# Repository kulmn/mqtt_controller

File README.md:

# External device controller with timers and MQTT protocol.

Hardware: 
- Schematic diagram (Autodesk EAGLE) in /schematic/ dir
- MCU: STM32L152CB, STM32F030F4 ([firmware](https://github.com/kulmn/lcd_hd44780_f030x4))
- Ethernet: WIZnet W5500
- Indicator: HD44780 16x2

Firmware:
- GCC Eclipse project, FreeRTOS, LibOpenCM3

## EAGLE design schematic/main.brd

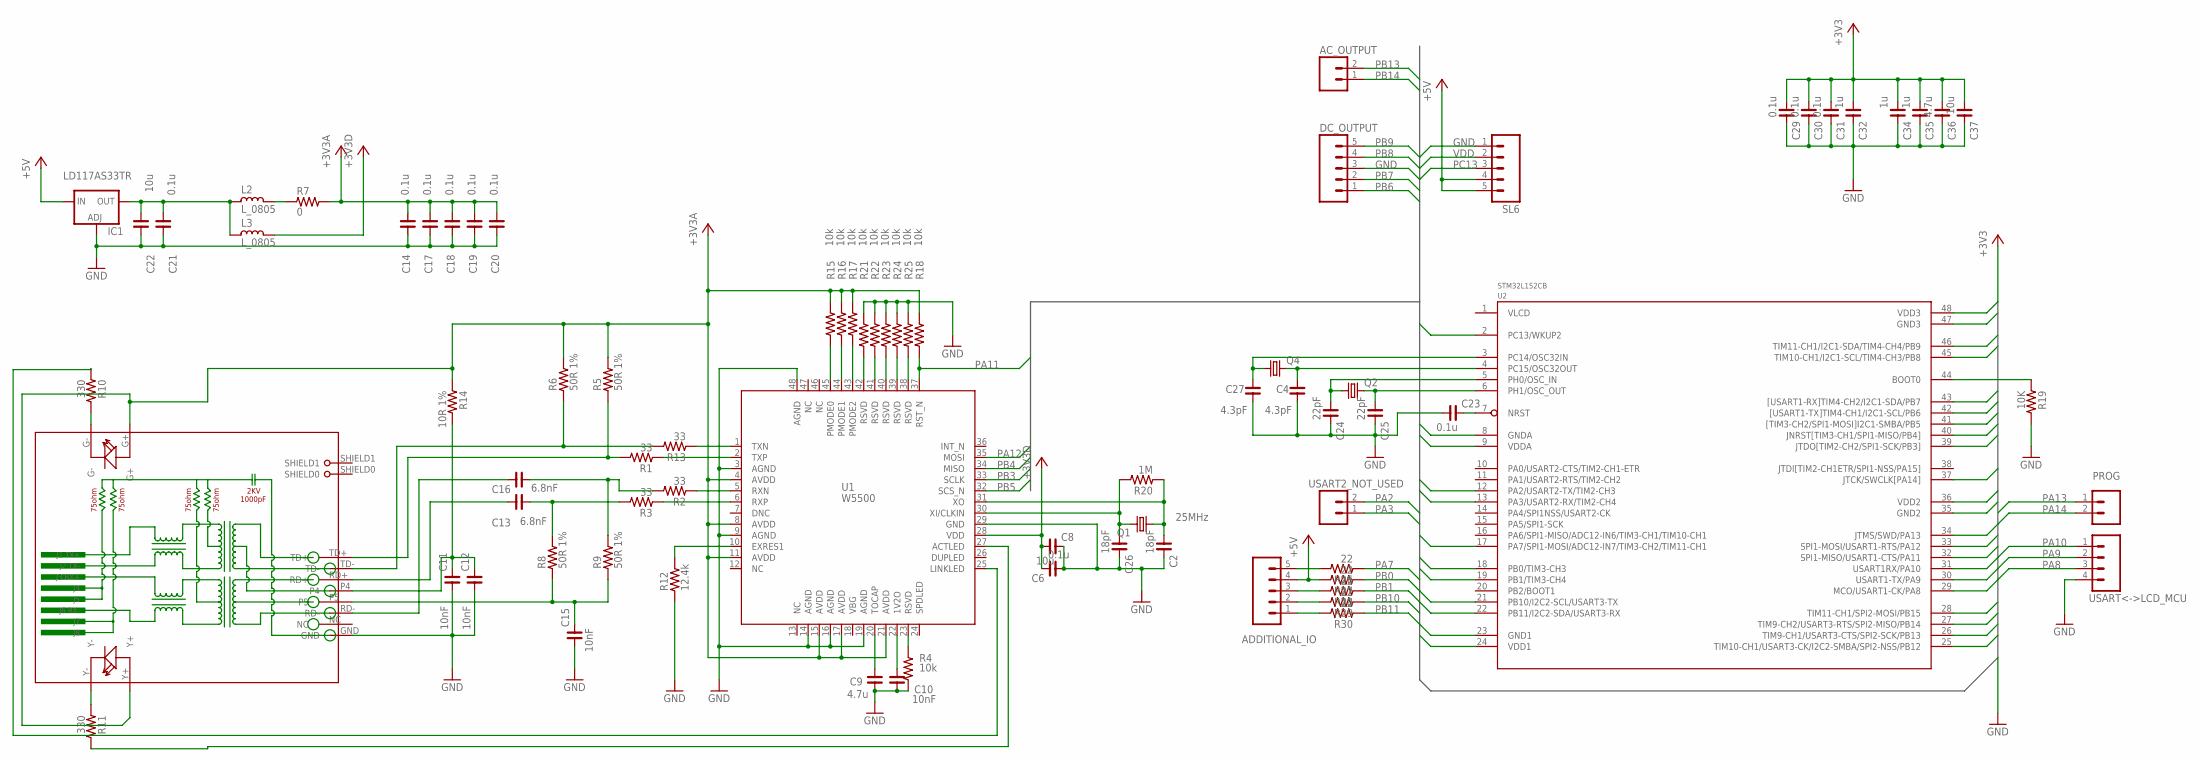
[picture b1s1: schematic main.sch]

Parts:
AC_OUTPUT: M02; 02P
ADDITIONAL_IO: M05; 05P
C2, C26: 18pF; C0603
C4, C27: 4.3pF; C0603
C6, C14, C17, C18, C19, C20, C21, C23, C29, C30, C31: 0.1u; C0805
C8, C22, C37: 10u; C0805
C9, C36: 4.7u; C0805
C10, C11, C12, C15: 10nF; C0603
C13, C16: 6.8nF; C0603
C24, C25: 22pF; C0805
C32, C34, C35: 1u; C0805
DC_OUTPUT: M05; 05P
IC1: LD117AS33TR; SOT223
L2, L3: L_0805; L0805
PROG: M02; 02P
Q1: 25MHz; HC49U-V
Q2: CRYSTALHC49U-V; HC49U-V
Q4: CRYSTALTC26H; TC26H
R1, R2, R3, R13: 33; R0603
R4, R15, R16, R17, R18, R21, R22, R23, R24, R25: 10k; R0603
R5, R6, R8, R9: 50R 1%; R0603
R7: 0; R1206
R10, R11: 330; R0805
R12: 12.4k; R0805
R14: 10R 1%; R0603
R19: 10K; R1206
R20: 1M; R0805
R26, R27, R28, R29, R30: 22; R0805
RJ1: HR911105A
SL6: M05; 05P
U1: W5500
U2: STM32L152CB; LQFP48-7X7
USART2_NOT_USED: M02; 02P
USART<->LCD_MCU: M04; 04P

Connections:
+3V3A: C14.1, C17.1, C18.1, C19.1, C20.1, R5.2, R6.2, R7.2, R14.1, R15.2, R16.2, R17.2, R18.2, RJ1.G+, RJ1.Y+, U1.4 (AVDD), U1.8 (AVDD), U1.11 (AVDD), U1.15 (AVDD), U1.17 (AVDD), U1.21 (AVDD)
+3V3D: C6.2, C8.1, L3.1, U1.28 (VDD)
+5V: ADDITIONAL_IO.4, IC1.3 (IN), R27.2, SL6.4, SL6.5
GND: C2.2, C4.1, C6.1, C8.2, C9.2, C10.1, C11.1, C12.1, C14.2, C15.1, C17.2, C18.2, C19.2, C20.2, C21.2, C22.2, C23.1, C24.2, C25.2, C26.2, C27.1, C29.2, C30.2, C31.2, C32.2, C34.2, C35.2, C36.2, C37.2, DC_OUTPUT.3, IC1.1 (ADJ), R4.2, R12.1, R19.2, R21.2, R22.2, R23.2, R24.2, R25.2, RJ1.GND, SL6.1, U1.3 (AGND), U1.9 (AGND), U1.14 (AGND), U1.16 (AGND), U1.19 (AGND), U1.29 (GND), U1.48 (AGND), U2.8 (GNDA), U2.23 (GND1), U2.35 (GND2), U2.47 (GND3), USART<->LCD_MCU.4
unnamed: C9.1, U1.20 (TOCAP)
unnamed: C10.2, U1.22 (1V2O)
unnamed: R13.1, U1.1 (TXN)
unnamed: C2.1, Q1.1, R20.1, U1.31 (XO)
unnamed: C26.1, Q1.2, R20.2, U1.30 (XI/CLKIN)
unnamed: R1.1, U1.2 (TXP)
unnamed: R2.1, U1.5 (RXN)
unnamed: R3.1, U1.6 (RXP)
unnamed: R4.1, U1.23 (RSVD)
unnamed: C21.1, C22.1, IC1.4 (OUT), L2.2, L3.2
unnamed: C16.1, R2.2, R9.2
unnamed: C13.1, R3.2, R8.2
unnamed: L2.1, R7.1
unnamed: R10.2, RJ1.G-
unnamed: C11.2, C12.2, R14.2, RJ1.P4
unnamed: R11.1, RJ1.Y-
unnamed: R6.1, R13.2, RJ1.TD-
unnamed: C13.2, RJ1.RD+
unnamed: R10.1, U1.25 (LINKLED)
unnamed: R11.2, U1.27 (ACTLED)
unnamed: R16.1, U1.44 (PMODE1)
unnamed: R15.1, U1.45 (PMODE0)
unnamed: R17.1, U1.43 (PMODE2)
unnamed: C16.2, RJ1.RD-
unnamed: R12.2, U1.10 (EXRES1)
unnamed: R1.2, R5.1, RJ1.TD+
unnamed: C15.2, R8.1, R9.1, RJ1.P5
unnamed: ADDITIONAL_IO.5, R26.2
unnamed: C23.2, U2.7 (NRST)
unnamed: R19.1, U2.44 (BOOT0)
unnamed: C27.2, Q4.1, U2.3 (PC14/OSC32IN)
unnamed: C24.1, Q2.1, U2.5 (PH0/OSC_IN)
unnamed: C25.1, Q2.2, U2.6 (PH1/OSC_OUT)
unnamed: C4.2, Q4.2, U2.4 (PC15/OSC32OUT)
unnamed: ADDITIONAL_IO.3, R28.2
unnamed: ADDITIONAL_IO.2, R29.2
unnamed: R21.1, U1.42 (RSVD)
unnamed: R22.1, U1.41 (RSVD)
unnamed: R23.1, U1.40 (RSVD)
unnamed: R24.1, U1.39 (RSVD)
unnamed: R25.1, U1.38 (RSVD)
unnamed: ADDITIONAL_IO.1, R30.2
PA2: U2.12 (PA2/USART2-TX/TIM2-CH3), USART2_NOT_USED.2
PA3: U2.13 (PA3/USART2-RX/TIM2-CH4), USART2_NOT_USED.1
PA7: R26.1, U2.17 (PA7/SPI1-MOSI/ADC12-IN7/TIM3-CH2/TIM11-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)
PA8: U2.29 (MCO/USART1-CK/PA8), USART<->LCD_MCU.3
PA9: U2.30 (USART1-TX/PA9), USART<->LCD_MCU.2
PA10: U2.31 (USART1RX/PA10), USART<->LCD_MCU.1
PA11: R18.1, U1.37 (RST_N), U2.32 (SPI1-MISO/USART1-CTS/PA11)
PA12: U1.35 (MOSI), U2.33 (SPI1-MOSI/USART1-RTS/PA12)
PA13: PROG.1, U2.34 (JTMS/SWD/PA13)
PA14: PROG.2, U2.37 (JTCK/SWCLK[PA14])
PB0: R27.1, U2.18 (PB0/TIM3-CH3)
PB1: R28.1, U2.19 (PB1/TIM3-CH4)
PB3: U1.33 (SCLK), U2.39 (JTDO[TIM2-CH2/SPI1-SCK/PB3])
PB4: U1.34 (MISO), U2.40 (JNRST[TIM3-CH1/SPI1-MISO/PB4])
PB5: U1.32 (SCS_N), U2.41 ([TIM3-CH2/SPI1-MOSI]I2C1-SMBA/PB5)
PB6: DC_OUTPUT.1, U2.42 ([USART1-TX]TIM4-CH1/I2C1-SCL/PB6)
PB7: DC_OUTPUT.2, U2.43 ([USART1-RX]TIM4-CH2/I2C1-SDA/PB7)
PB8: DC_OUTPUT.4, U2.45 (TIM10-CH1/I2C1-SCL/TIM4-CH3/PB8)
PB9: DC_OUTPUT.5, U2.46 (TIM11-CH1/I2C1-SDA/TIM4-CH4/PB9)
PB10: R29.1, U2.21 (PB10/I2C2-SCL/USART3-TX)
PB11: R30.1, U2.22 (PB11/I2C2-SDA/USART3-RX)
PB12: U2.25 (TIM10-CH1/USART3-CK/I2C2-SMBA/SPI2-NSS/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)
PB13: AC_OUTPUT.2, U2.26 (TIM9-CH1/USART3-CTS/SPI2-SCK/PB13)
PB14: AC_OUTPUT.1, U2.27 (TIM9-CH2/USART3-RTS/SPI2-MISO/PB14)
PB15: U2.28 (TIM11-CH1/SPI2-MOSI/PB15)
PC13: SL6.3, U2.2 (PC13/WKUP2)
VDD: C29.1, C30.1, C31.1, C32.1, C34.1, C35.1, C36.1, C37.1, SL6.2, U2.9 (VDDA), U2.24 (VDD1), U2.36 (VDD2), U2.48 (VDD3)

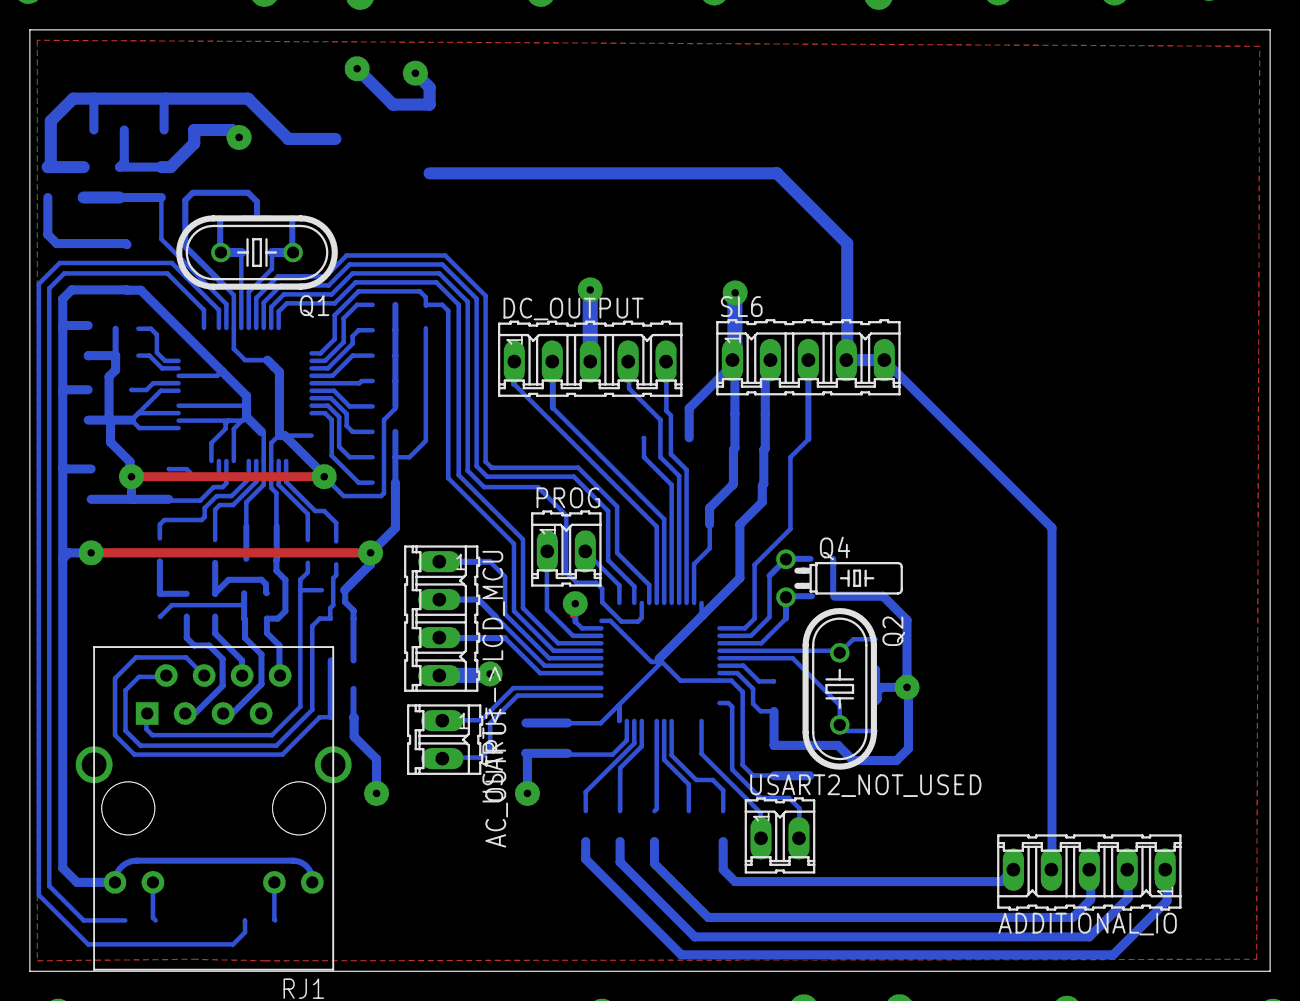
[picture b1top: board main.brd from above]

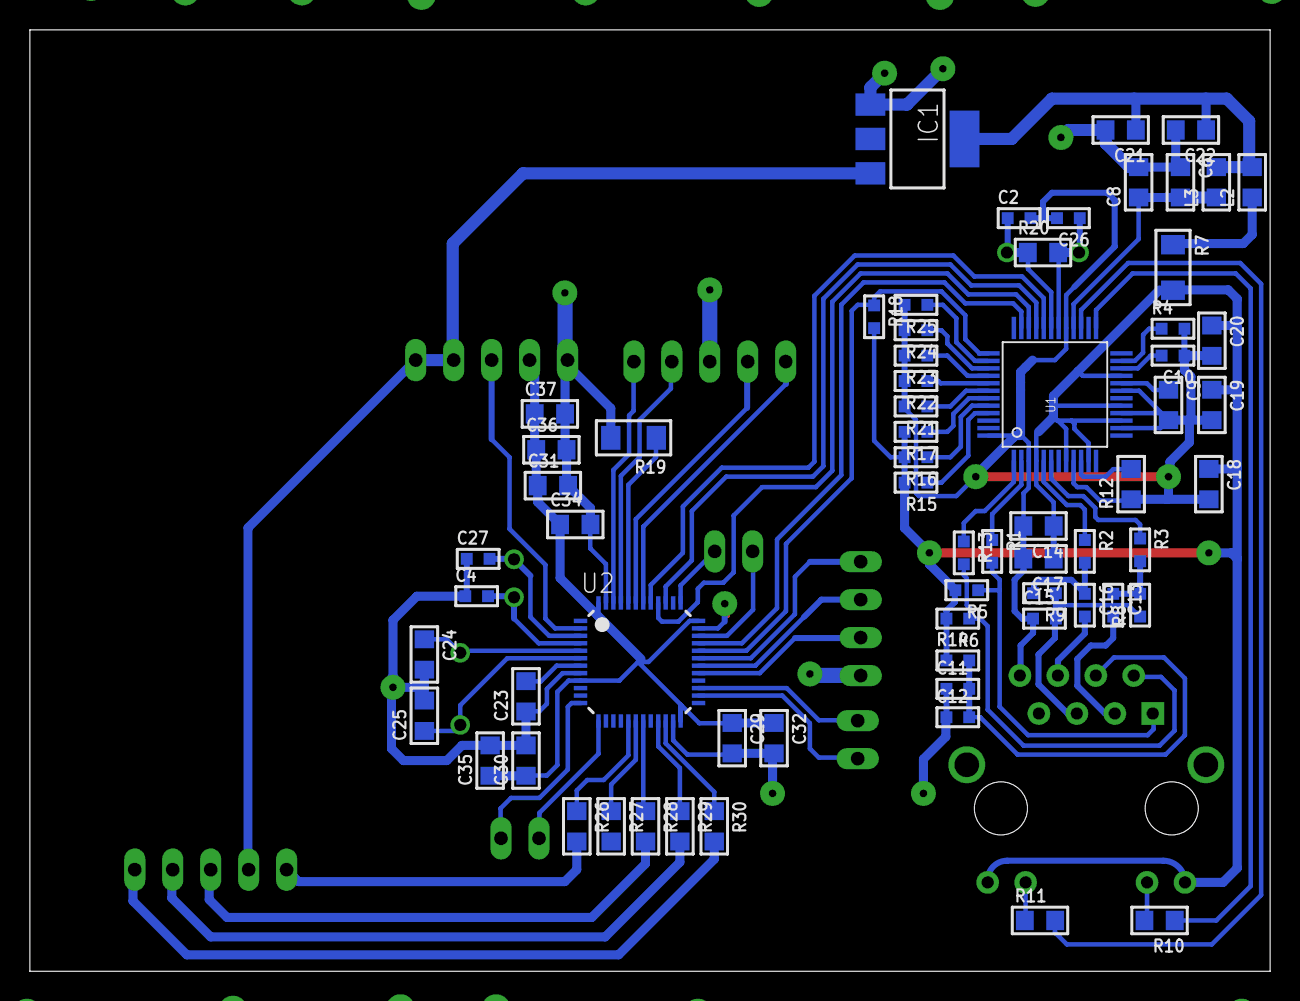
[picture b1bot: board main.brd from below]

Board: 2 copper layers, 83.0 x 63.0 mm, 77 parts (66 on the bottom side), 71 nets.

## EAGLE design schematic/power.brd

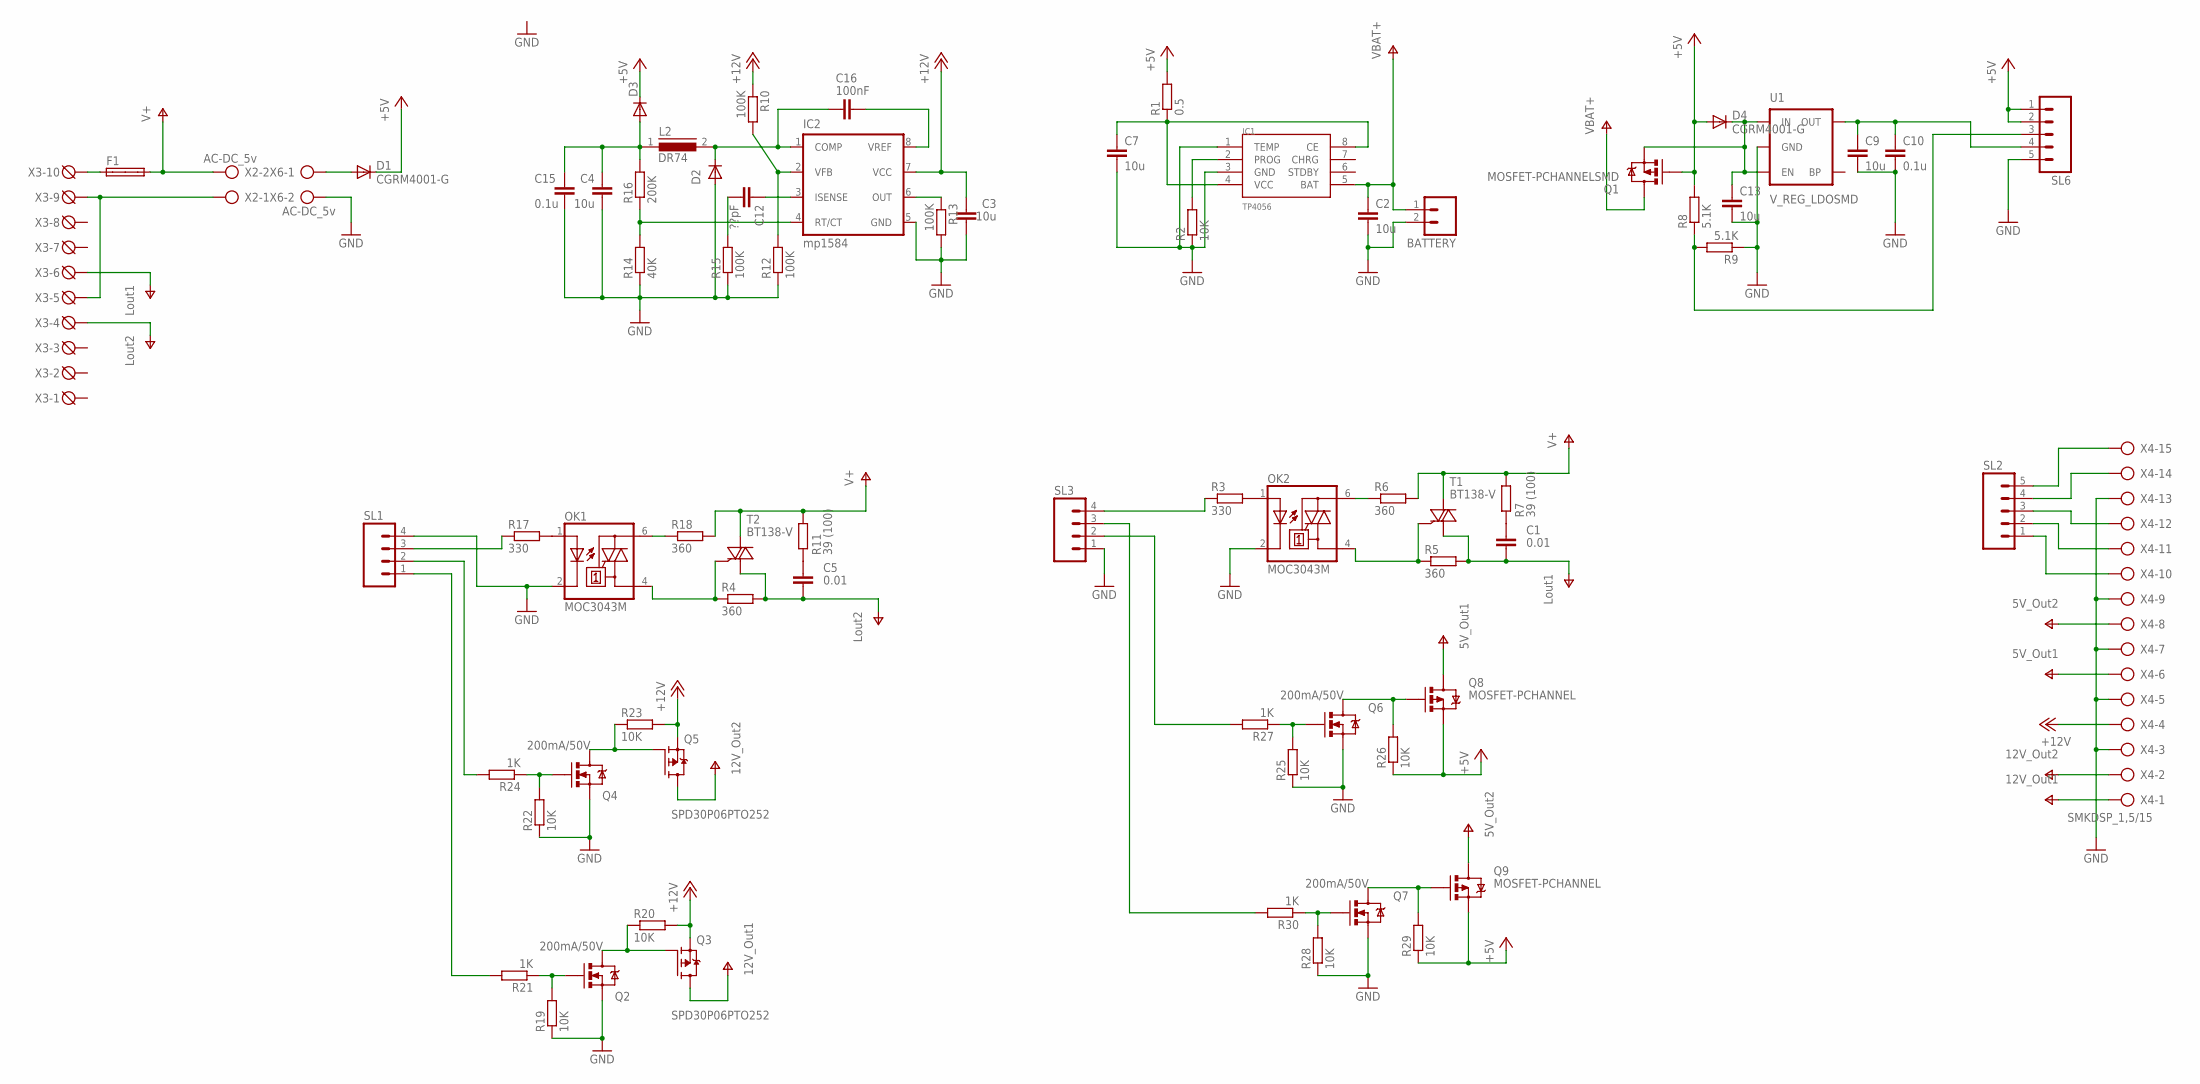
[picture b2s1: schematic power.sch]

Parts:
BATTERY: M02; 02P
C1, C5: 0.01; C075-032X103
C2, C7, C9, C13: 10u; C0805
C3, C4: 10u; C1206
C10, C15: 0.1u; C0805
C12: ??pF; C0603
C16: 100nF; C0603
D1, D3, D4: CGRM4001-G; SOD-123_MINI-SMA
D2: ES2D; SMB
F1: SHK20L
IC1: TP4056; SOP-8
IC2: mp1584; SO-08
L2: DR74
OK1, OK2: MOC3043M; DIL06
Q1: MOSFET-PCHANNELSMD; SOT23-3
Q2, Q4, Q6, Q7: 200mA/50V; SOT23-3
Q3, Q5: SPD30P06PTO252; TO252
Q8, Q9: MOSFET-PCHANNEL; SOT23-3
R1: 0.5; R0805
R2, R19, R20, R22, R23, R25, R26, R28, R29: 10K; R0805
R3, R17: 330; R1206
R4, R5: 360; 0204/7
R6, R18: 360; R1206
R7, R11: 39 (100); 0411/12
R8, R9: 5.1K; R0805
R10, R12, R13, R15: 100K; R0603
R14: 40K; R0603
R16: 200K; R0603
R21, R24, R27, R30: 1K; R0805
SL1, SL3: M04; 04P
SL2, SL6: M05; 05P
T1, T2: BT138-V; TO220BV
U1: V_REG_LDOSMD; SOT23-5
X2, X6: AC-DC_5v; AK300/2
X3: DG3XX-10; DG129-7.5-10P
X4: SMKDSP_1,5/15

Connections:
5V_OUT1: Q8.3 (D), X4.6
5V_OUT2: Q9.3 (D), X4.8
12V_OUT1: Q3.3 (D), X4.1
12V_OUT2: Q5.3 (D), X4.2
+5V: D1.C, D3.C, D4.A, Q1.1 (G), Q8.2 (S), Q9.2 (S), R1.2, R8.2, R26.1, R29.1, SL6.1, SL6.2
+12V: C3.2, IC2.7 (VCC), Q3.2 (S), Q5.2 (S), R10.1, R20.2, R23.2, X4.4
GND: BATTERY.2, C2.2, C3.1, C4.1, C7.2, C9.2, C10.2, C13.2, C15.2, D2.A, IC1.1 (TEMP), IC1.3 (GND), IC2.5 (GND), OK1.2 (C), OK2.2 (C), Q2.2 (S), Q4.2 (S), Q6.2 (S), Q7.2 (S), R2.1, R9.1, R12.1, R13.2, R14.1, R15.1, R19.1, R22.1, R25.1, R28.1, SL1.4, SL3.1, SL6.5, U1.2 (GND), X4.3, X4.5, X4.7, X4.9, X4.13, X6.2
LOUT1: C1.2, R5.2, T1.T1 (A1), X3.6
LOUT2: C5.2, R4.2, T2.T1 (A1), X3.4
unnamed: OK2.4 (A1), R5.1, T1.G
unnamed: IC1.2 (PROG), R2.2
unnamed: C7.1, IC1.4 (VCC), IC1.8 (CE), R1.1
unnamed: OK2.6 (A2), R6.1
unnamed: C9.1, C10.1, SL6.4, U1.5 (OUT)
unnamed: X2.1, X3.5, X3.9
unnamed: F1.1A, X3.10
unnamed: R30.2, SL3.3
unnamed: OK1.4 (A1), R4.1, T2.G
unnamed: C1.1, R7.1
unnamed: D1.A, X6.1
unnamed: C13.1, D4.C, Q1.2 (S), U1.1 (IN), U1.3 (EN)
unnamed: R8.1, R9.2, SL6.3
unnamed: OK2.1 (A), R3.2
unnamed: R27.2, SL3.2
unnamed: IC2.2 (VFB), R10.2, R12.2
unnamed: IC2.6 (OUT), R13.1
unnamed: IC2.4 (RT/CT), R14.2, R16.1
unnamed: C12.2, R15.2
unnamed: C12.1, IC2.3 (ISENSE)
unnamed: C16.1, IC2.8 (VREF)
unnamed: C5.1, R11.1
unnamed: Q2.3 (D), Q3.1 (G), R20.1
unnamed: C4.2, C15.1, D3.A, L2.1, R16.2
unnamed: C16.2, D2.C, IC2.1 (COMP), L2.2
unnamed: R17.1, SL1.3
unnamed: Q6.3 (D), Q8.1 (G), R26.2
unnamed: OK1.1 (A), R17.2
unnamed: SL2.1, X4.10
unnamed: OK1.6 (A2), R18.1
unnamed: Q2.1 (G), R19.2, R21.1
unnamed: Q4.3 (D), Q5.1 (G), R23.1
unnamed: Q4.1 (G), R22.2, R24.1
unnamed: Q6.1 (G), R25.2, R27.1
unnamed: Q7.1 (G), R28.2, R30.1
unnamed: Q7.3 (D), Q9.1 (G), R29.2
unnamed: R24.2, SL1.2
unnamed: R21.2, SL1.1
unnamed: R3.1, SL3.4
unnamed: SL2.2, X4.11
unnamed: SL2.3, X4.12
unnamed: SL2.4, X4.14
unnamed: SL2.5, X4.15
V+: F1.2A, R6.2, R7.2, R11.2, R18.2, T1.T2 (A2), T2.T2 (A2), X2.2
VBAT: BATTERY.1, C2.1, IC1.5 (BAT), Q1.3 (D)

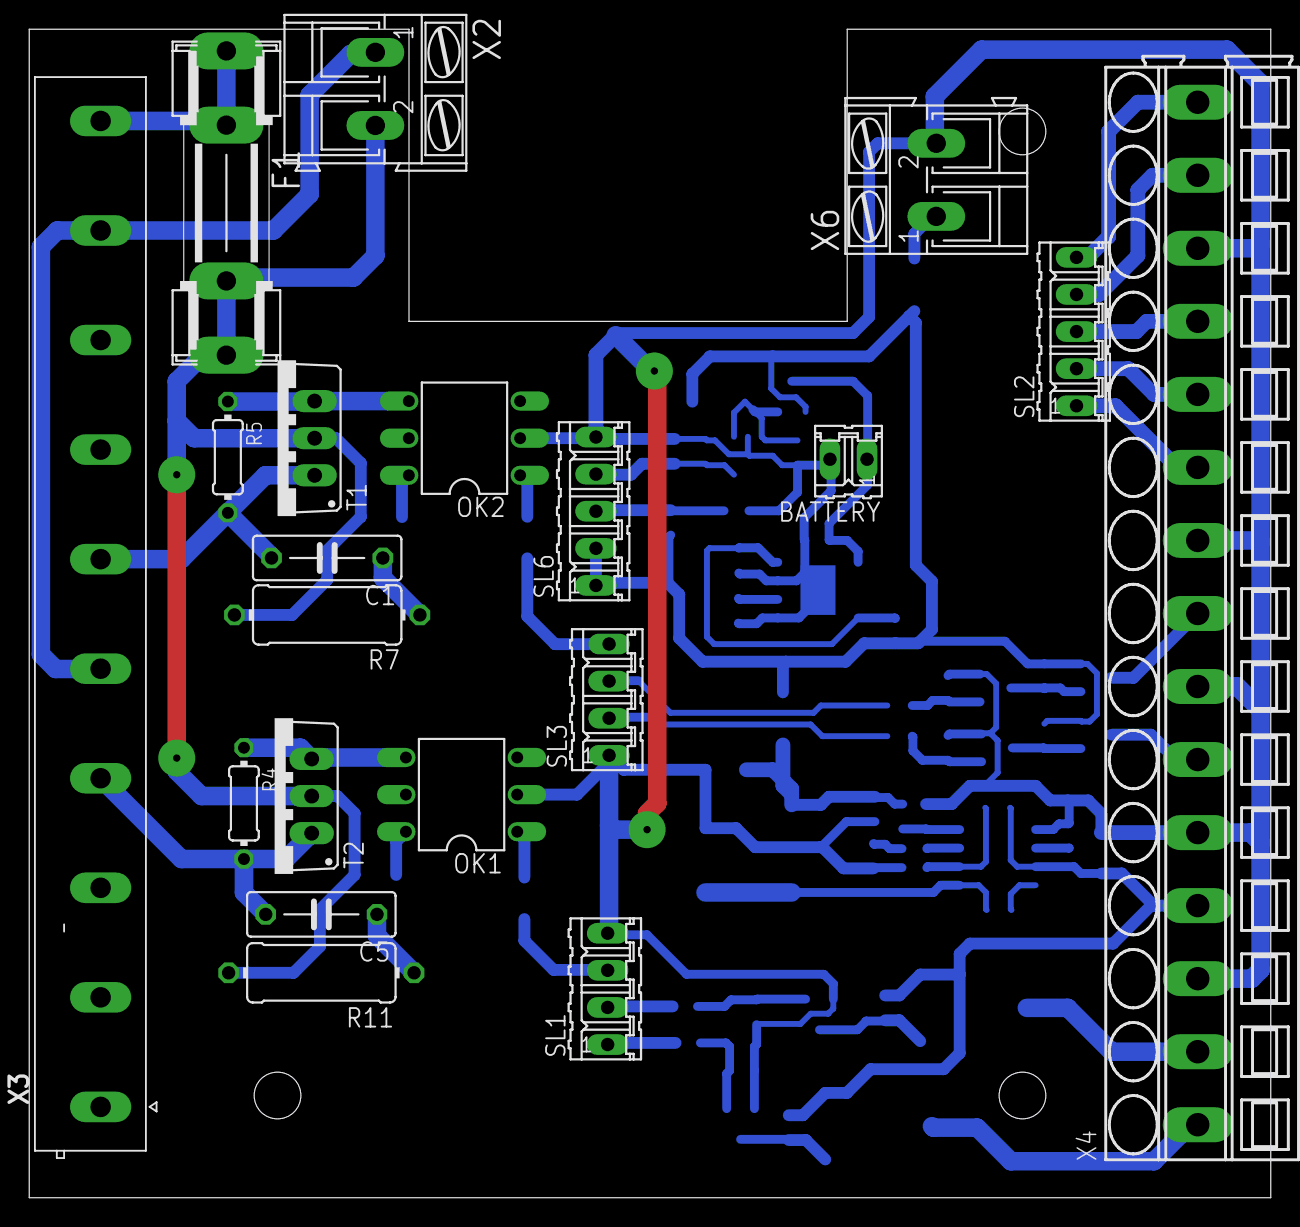
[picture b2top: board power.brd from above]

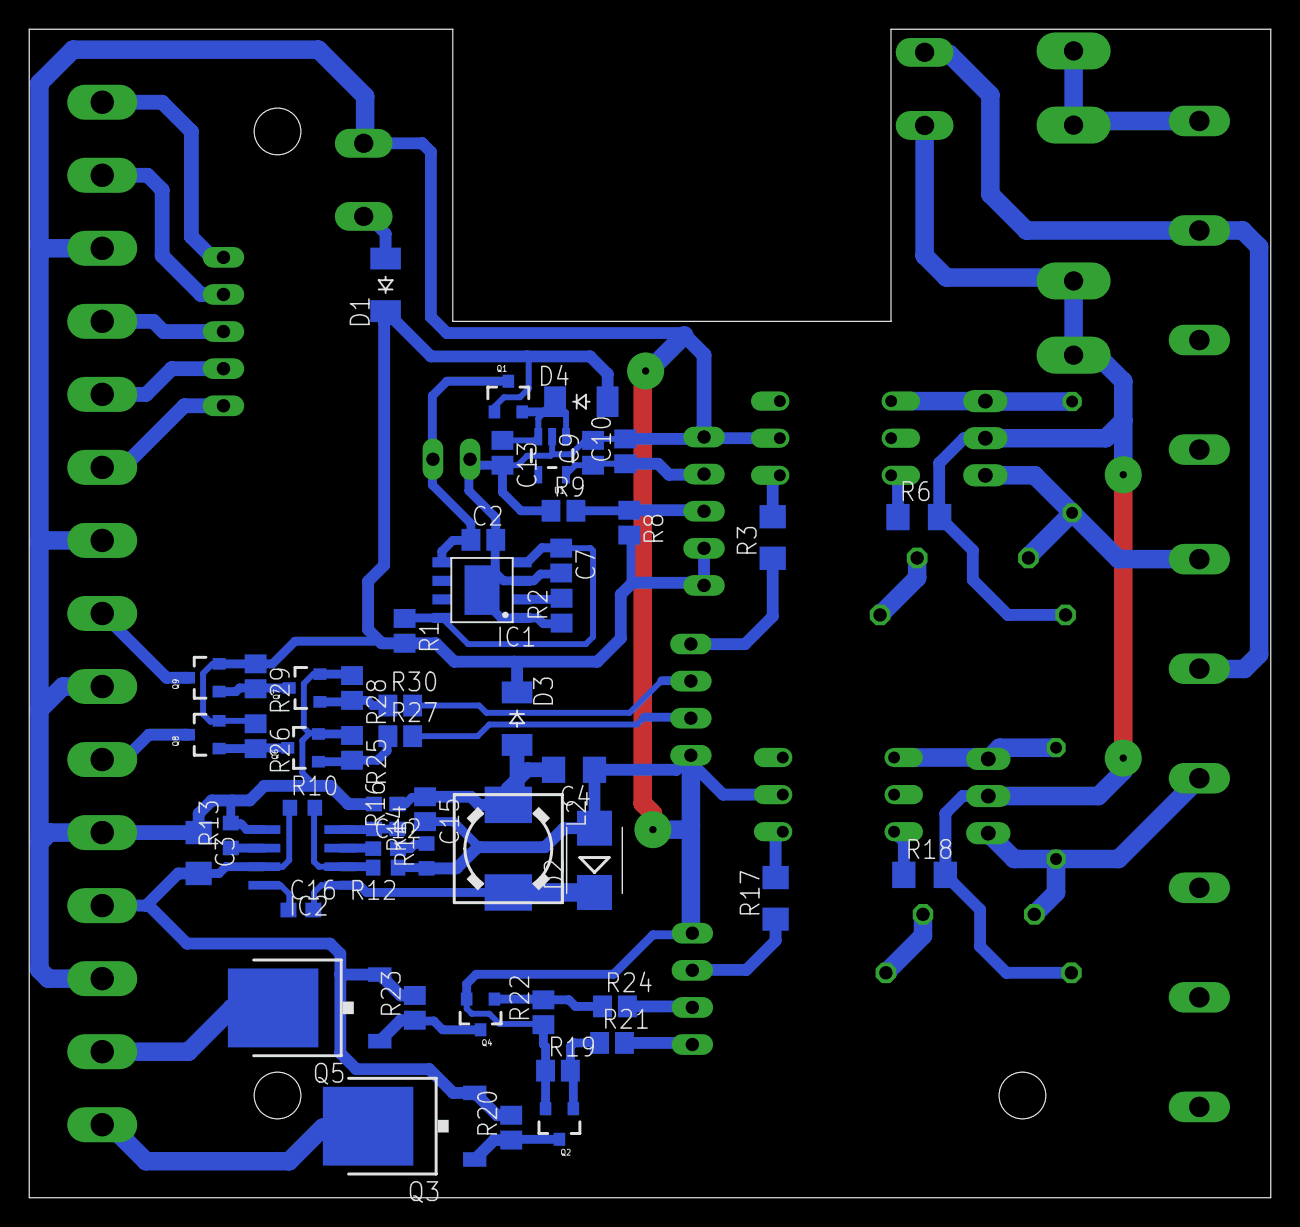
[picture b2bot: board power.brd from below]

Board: 2 copper layers, 85.0 x 80.0 mm, 73 parts (53 on the bottom side), 54 nets.

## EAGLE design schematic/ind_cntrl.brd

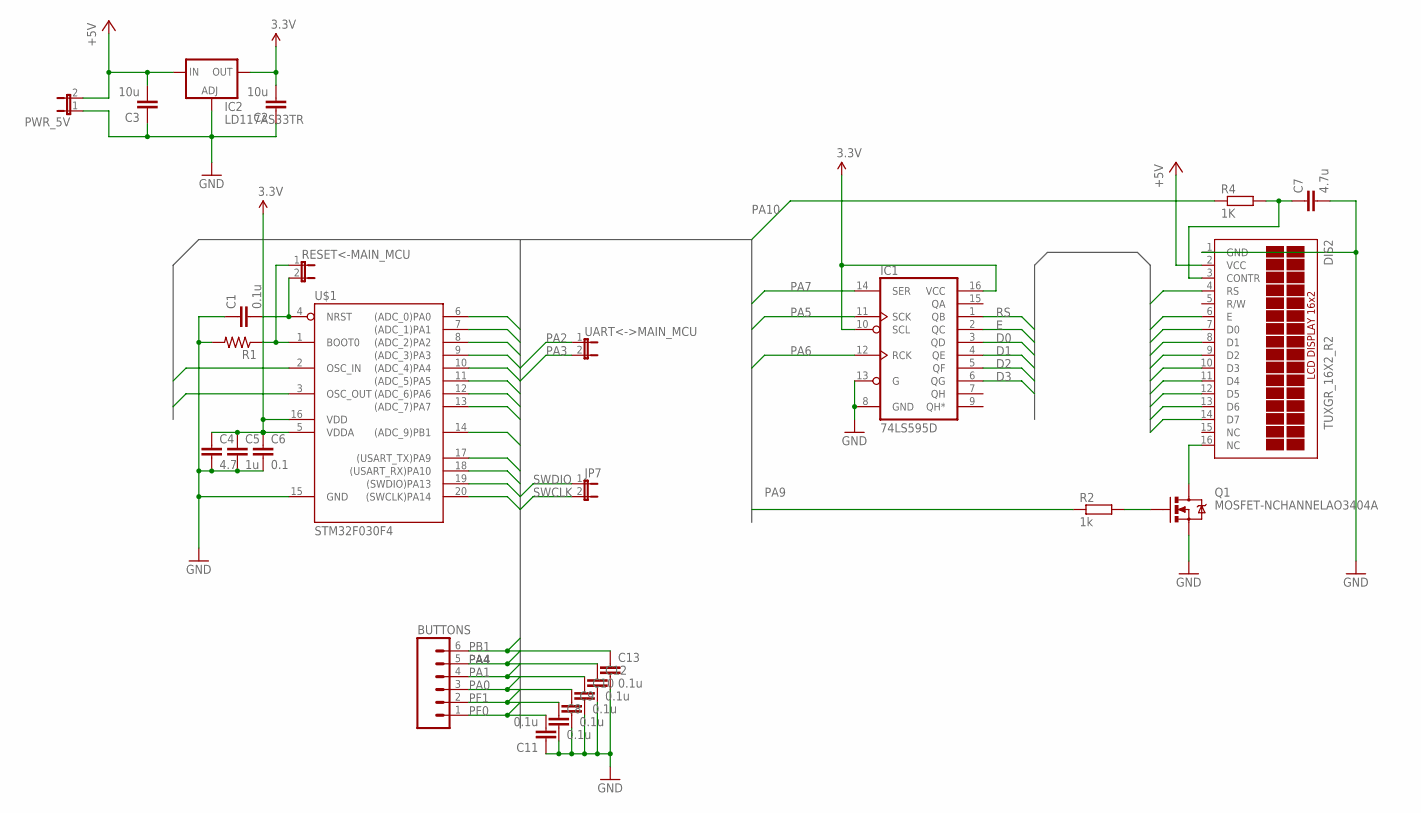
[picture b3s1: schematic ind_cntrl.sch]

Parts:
BUTTONS: M06; 06P
C1, C8, C9, C10, C11, C12, C13: 0.1u; 0805
C2, C3: 10u; 0805
C4: 4.7; 0805
C5: 1u; 0805
C6: 0.1; 0805
C7: 4.7u; C1206
DIS2: TUXGR_16X2_R2
IC1: 74LS595D; SO16
IC2: LD117AS33TR; SOT223
JP7: JP1E; JP1
PWR_5V: JP1E; JP1
Q1: MOSFET-NCHANNELAO3404A; SOT23-3
R1: RESISTOR0805-RES; 0805
R2: 1k; R0805
R4: 1K; R0805
RESET<-MAIN_MCU: JP1E; JP1
U$1: STM32F030F4; 2QSP20
UART<->MAIN_MCU: JP1E; JP1

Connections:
3.3V: C2.2, C4.1, C5.1, C6.1, IC1.10 (SCL), IC1.16 (VCC), IC2.4 (OUT), U$1.5 (VDDA), U$1.16 (VDD)
+5V: C3.2, DIS2.2 (VCC), IC2.3 (IN), PWR_5V.2
D0: DIS2.7 (D0), IC1.3 (QD)
D1: DIS2.8 (D1), IC1.4 (QE)
D2: DIS2.9 (D2), IC1.5 (QF)
D3: DIS2.10 (D3), IC1.6 (QG)
D4: DIS2.11 (D4)
D5: DIS2.12 (D5)
D6: DIS2.13 (D6)
D7: DIS2.14 (D7)
E: DIS2.6 (E), IC1.2 (QC)
GND: C1.1, C2.1, C3.1, C4.2, C5.2, C6.2, C7.2, C8.2, C9.2, C10.2, C11.1, C12.2, C13.2, DIS2.1 (GND), IC1.8 (GND), IC1.13 (G), IC2.1 (ADJ), PWR_5V.1, Q1.2 (S), R1.2, U$1.15 (GND)
unnamed: C1.2, RESET<-MAIN_MCU.2, U$1.4 (NRST)
unnamed: R1.1, RESET<-MAIN_MCU.1, U$1.1 (BOOT0)
unnamed: C7.1, DIS2.3 (CONTR), R4.2
unnamed: Q1.1 (G), R2.2
unnamed: DIS2.16 (NC), Q1.3 (D)
PA0: BUTTONS.3, C9.1, U$1.6 ((ADC_0)PA0)
PA1: BUTTONS.4, C10.1, U$1.7 ((ADC_1)PA1)
PA2: U$1.8 ((ADC_2)PA2), UART<->MAIN_MCU.1
PA3: U$1.9 ((ADC_3)PA3), UART<->MAIN_MCU.2
PA4: BUTTONS.5, C12.1, U$1.10 ((ADC_4)PA4)
PA5: IC1.11 (SCK), U$1.11 ((ADC_5)PA5)
PA6: IC1.12 (RCK), U$1.12 ((ADC_6)PA6)
PA7: IC1.14 (SER), U$1.13 ((ADC_7)PA7)
PA9: R2.1, U$1.17 ((USART_TX)PA9)
PA10: R4.1, U$1.18 ((USART_RX)PA10)
PB1: BUTTONS.6, C13.1, U$1.14 ((ADC_9)PB1)
PF0: BUTTONS.1, C11.2, U$1.2 (OSC_IN)
PF1: BUTTONS.2, C8.1, U$1.3 (OSC_OUT)
RS: DIS2.4 (RS), IC1.1 (QB)
SWCLK: JP7.2, U$1.20 ((SWCLK)PA14)
SWDIO: JP7.1, U$1.19 ((SWDIO)PA13)

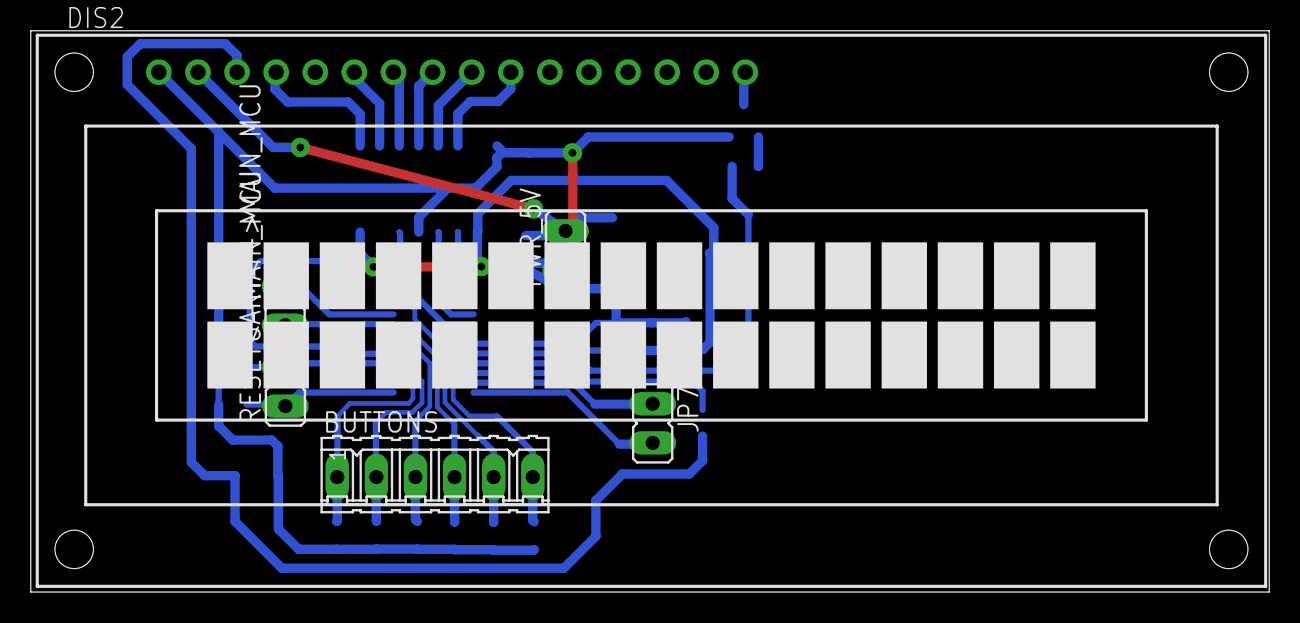
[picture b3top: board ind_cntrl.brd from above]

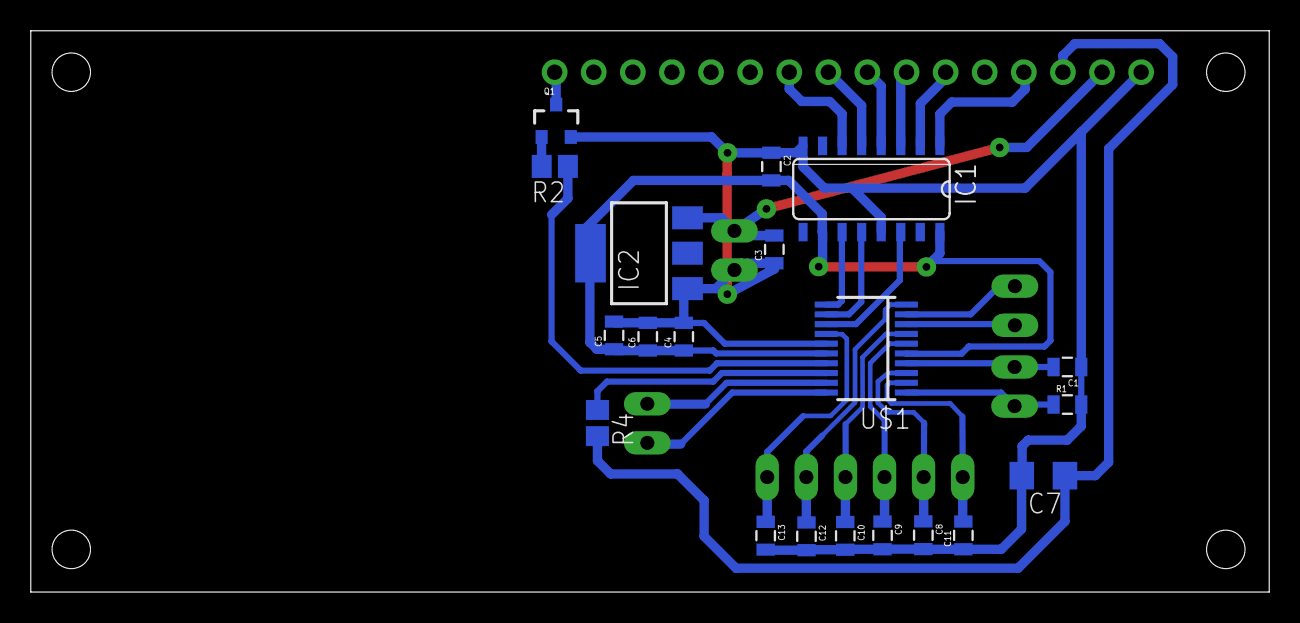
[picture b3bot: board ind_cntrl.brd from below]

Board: 2 copper layers, 80.5 x 36.5 mm, 26 parts (20 on the bottom side), 29 nets.

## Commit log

2021-03-02 init
2021-03-02 Create LICENSE

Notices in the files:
parts and their libraries:
SparkFun-Capacitors: Licensing: Creative Commons ShareAlike 4.0 International - https://creativecommons.org/licenses/by-sa/4.0
rc-master-smd: Copyright (C) 2007, Bob Starr
SparkFun: Licensing: CC v3.0 Share-Alike You are welcome to use this library for commercial purposes.
